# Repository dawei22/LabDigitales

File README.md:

#LabDigitales

Proyecto "Macetero Inteligente" para curso EL5202-1 Laboratorio de Sistemas Digitales. 

Control vía aplicación android de sensores en un macetero, controlados por arduino YUN. 
Diseño de PCB en Eagle para Shield de Arduino YUN

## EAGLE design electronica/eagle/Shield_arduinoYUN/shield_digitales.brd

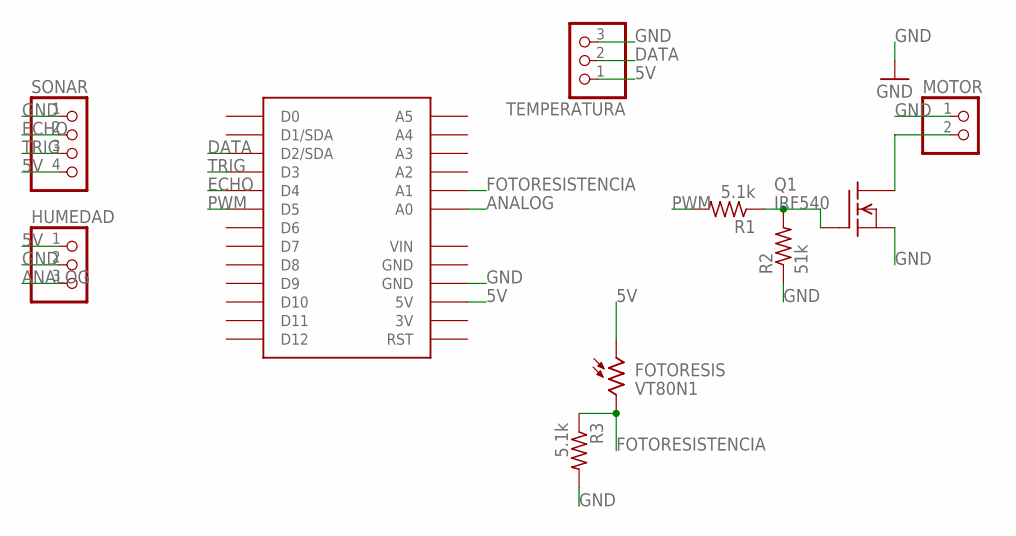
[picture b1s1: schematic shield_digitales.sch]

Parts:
FOTORESIS: VT80N1; VT800
HUMEDAD: PINHD-1X3; 1X03
MOTOR: PINHD-1X2; 1X02
Q1: IRF540; TO220
R1, R3: 5.1k; 0207/10
R2: 51k; 0207/10
SONAR: PINHD-1X4; 1X04
TEMPERATURA: PINHD-1X3; 1X03
U1: YUN_MINI_SHIELD-BPLACE; YUN_MINI_SHIELD

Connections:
3V: U1.3V
5V: FOTORESIS.1, HUMEDAD.1, SONAR.4, TEMPERATURA.1, U1.5V
ANALOG: HUMEDAD.3, U1.A0
DATA: TEMPERATURA.2, U1.D2 (D2/SDA)
ECHO: SONAR.2, U1.D4
FOTORESISTENCIA: FOTORESIS.2, R3.1, U1.A1
GND: HUMEDAD.2, MOTOR.1, Q1.3 (S), R2.1, R3.2, SONAR.1, TEMPERATURA.3, U1.GND1 (GND), U1.GND2 (GND)
unnamed: Q1.1 (G), R1.1, R2.2
unnamed: MOTOR.2, Q1.2 (D)
PWM: R1.2, U1.D5
TRIG: SONAR.3, U1.D3
VIN: U1.VIN

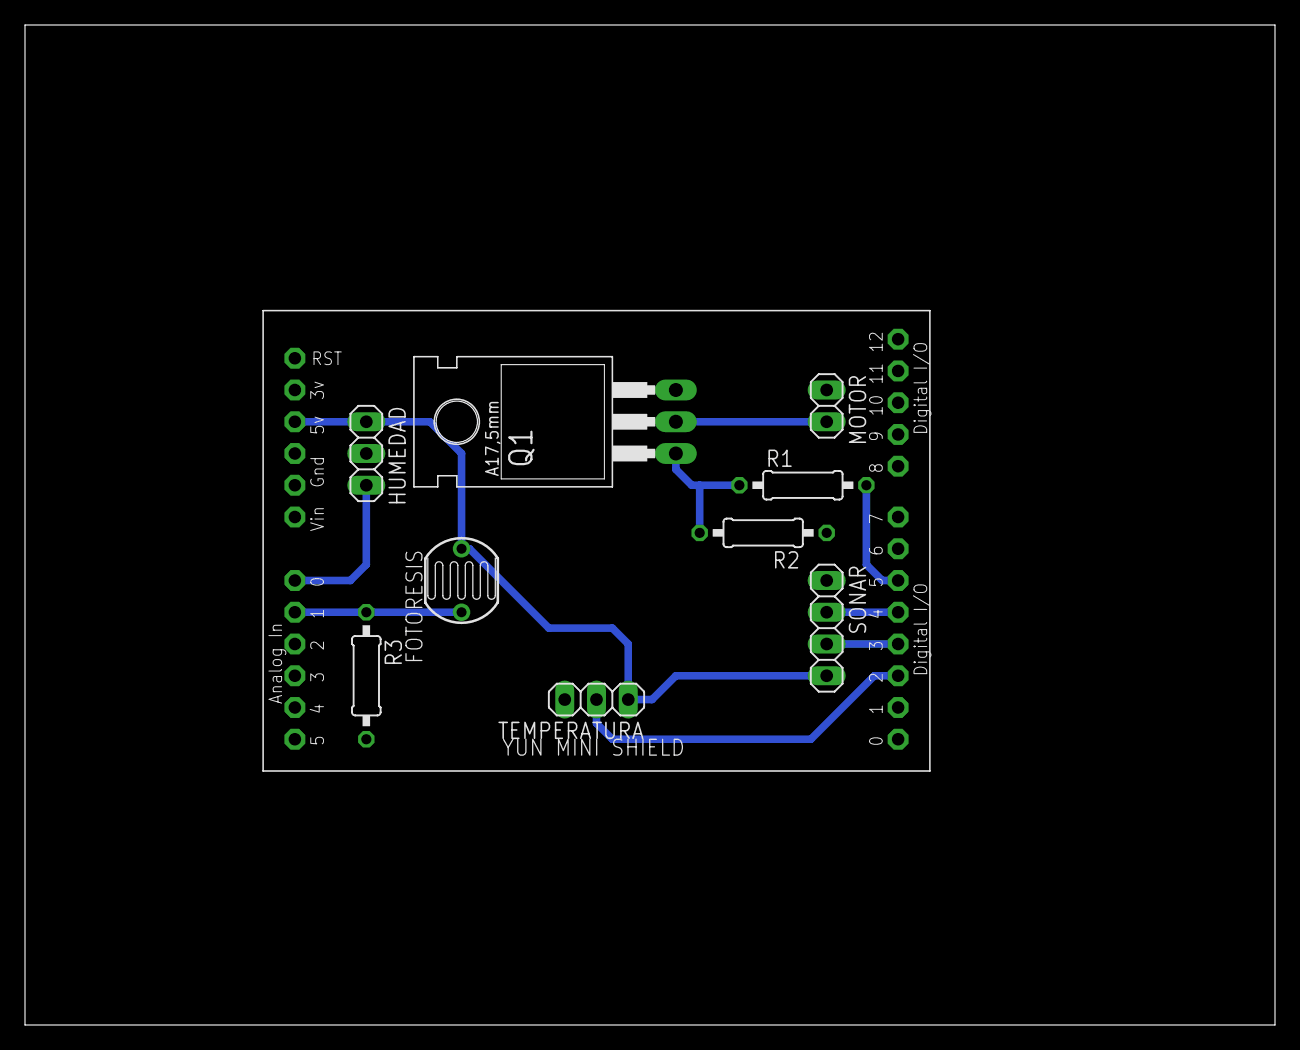
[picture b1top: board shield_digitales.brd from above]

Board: 2 copper layers, 100.0 x 80.0 mm, 10 parts (0 on the bottom side), 10 nets.

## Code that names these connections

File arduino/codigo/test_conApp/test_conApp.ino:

#include <NewPing.h>
#include "DHT.h" 
#include <Bridge.h>
#include "HttpClient.h"
#include <BridgeServer.h>
#include <BridgeClient.h>
#include <Thread.h>

// Listen to the default port 5555, the Yún webserver
// will forward there all the HTTP requests you send
BridgeServer server;

Thread appThread = Thread();

void callback() {
   BridgeClient client = server.accept();

  // There is a new client?
  if (client) {
    // Process request
    process(client);
          Serial.print("COOL! I'm running on: ");
    Serial.println(millis());

    // Close connection and free resources.
    client.stop();

  }

  
}

//thingspeak
String thingspeak_write_API_key = "FSHJLAKF63DIZ9N2";

//dht
#define DHTPIN 7  
#define DHTTYPE DHT11
DHT dht(DHTPIN, DHTTYPE);

//sonar
#define TRIG 3
#define ECHO 4
NewPing sonar(TRIG,ECHO,25);

//bomba
#define PWM  5

//humedad tierra
#define HT 7

//arreglo
#define ARRAYLENGTH 3

//#define interruptPin 2;

//inicializar maq. estado
int state = 0;


void setup() {
  // Initialize Bridge
  Bridge.begin();
  // Initialize Console
  Console.begin();
  //inicializar dht
  dht.begin();
  //setup sonar
  pinMode(ECHO, INPUT);
  pinMode(TRIG,OUTPUT);
  //bomba
  pinMode(PWM, OUTPUT);
  //humedad tierra
  pinMode(HT, INPUT);
  //fotorresitencia
  pinMode(A1, INPUT);
  //led13
  pinMode(13, OUTPUT);
  //analogo sonar
  pinMode(A3, OUTPUT);


  appThread.onRun(callback);
  appThread.setInterval(2000);
  appThread.enabled = true;

  


// const byte ledPin = 13;
//const byte interruptPin = 2;
////volatile bytze state = LOW;
//
//void setup() {
//  pinMode(ledPin, OUTPUT);
//  pinMode(interruptPin, INPUT_PULLUP);
//  attachInterrupt(digitalPinToInterrupt(interruptPin), blink, CHANGE);
//}
//
//void loop() {
//  digitalWrite(ledPin, state);
//}
//
//void blink() {
//  state = !state;
//}

  // Listen for incoming connection only from localhost
  // (no one from the external network could connect)
  server.listenOnLocalhost();
  server.begin();
}

void loop() {
  if (appThread.shouldRun()) {
      appThread.run();
  }

   switch (state){
    case 0:  // Medir 
if (analogRead(HT) > 600 && sonar.ping_cm()< 16){
        state = 1;
      }
      delay(50);
      break;

    case 1: // Regar
      analogWrite(PWM, 128);
      if (analogRead(HT) < 600){
        state = 2;
      }
      delay(50);
      break;

    case 2: // Imprimir
      analogWrite(PWM,0); //parar de regar
      float data[ARRAYLENGTH] = {dht.readHumidity(), dht.readTemperature(), promedioSonar(5)};
      float data[ARRAYLENGTH] = {50,20,10};
      postToThingSpeak(thingspeak_write_API_key, data);
      delay(1000); //cuanto espera para pasar al próximo estado 
      state = 0;
      break;
  }

}

void postToThingSpeak(String key, float value[]) {
  Process p;
  String cmd = "curl --data \"key="+key;
  for (int i=0;i<ARRAYLENGTH;i++) {
    cmd = cmd + "&field"+ (i+1) + "=" + value[i];
  }
  cmd = cmd + "\" http://api.thingspeak.com/update";
  p.runShellCommand(cmd);
  Console.println(cmd);
  p.close();
  }

float promedioSonar(int n) {
  float prom = 0;
  int i = 0;
  while (i < n){
    unsigned int nivel_cm  = sonar.ping_cm();
    prom = prom + nivel_cm;
    i++;
    delay(50);
  }
  return 20-prom/5;
}

void process(BridgeClient client) {
  // read the command
  String command = client.readStringUntil('/');

  // is "digital" command?
  if (command == "digital") {
    digitalCommand(client);
  }

  // is "analog" command?
  if (command == "analog") {
    analogCommand(client);
  }

  // is "mode" command?
  if (command == "mode") {
    modeCommand(client);
  }
}

void digitalCommand(BridgeClient client) {
  int pin, value;

  // Read pin number
  pin = client.parseInt();

  // If the next character is a '/' it means we have an URL
  // with a value like: "/digital/13/1"
  if (client.read() == '/') {
    value = client.parseInt();
    digitalWrite(pin, value);
  } else {
    value = digitalRead(pin);
  }

  // Send feedback to client
  client.print(F("Pin D"));
  client.print(pin);
  client.print(F(" set to "));
  client.println(value);

  // Update datastore key with the current pin value
  String key = "D";
  key += pin;
  Bridge.put(key, String(value));
}

void analogCommand(BridgeClient client) {
  int pin, value;

  // Read pin number
  pin = client.parseInt();

  // If the next character is a '/' it means we have an URL
  // with a value like: "/analog/5/120"
  if (client.read() == '/') {
    // Read value and execute command
    value = client.parseInt();
    analogWrite(pin, value);

    // Send feedback to client
    client.print(F("Pin D"));
    client.print(pin);
    client.print(F(" set to analog "));
    client.println(value);

    // Update datastore key with the current pin value
    String key = "D";
    key += pin;
    Bridge.put(key, String(value));
  } else {
    // Read analog pin
    value = analogRead(pin);

    // Send feedback to client
    client.print(F("Pin A"));
    client.print(pin);
    client.print(F(" reads analog "));
    client.println(value);

    // Update datastore key with the current pin value
    String key = "A";
    key += pin;
    Bridge.put(key, String(value));
  }
}

void sonarCommand(BridgeClient client) {
  int value, pin;
   pin = 3;
   value = promedioSonar(5);

   client.print(F("Sonar set to "));
   client.println(value);

    String key = "A";
    key += pin;
    Bridge.put(key, String(value));
  
  
}

void modeCommand(BridgeClient client) {
  int pin;

  // Read pin number
  pin = client.parseInt();

  // If the next character is not a '/' we have a malformed URL
  if (client.read() != '/') {
    client.println(F("error"));
    return;
  }

  String mode = client.readStringUntil('\r');

  if (mode == "input") {
    pinMode(pin, INPUT);
    // Send feedback to client
    client.print(F("Pin D"));
    client.print(pin);
    client.print(F(" configured as INPUT!"));
    return;
  }

  if (mode == "output") {
    pinMode(pin, OUTPUT);
    // Send feedback to client
    client.print(F("Pin D"));
    client.print(pin);
    client.print(F(" configured as OUTPUT!"));
    return;
  }

  client.print(F("error: invalid mode "));
  client.print(mode);
}

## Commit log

2016-06-03 placa
2016-06-03 codigo
2016-09-07 codigo final
